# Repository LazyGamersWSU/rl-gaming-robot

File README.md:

# RL Gaming Robot

The RL Gaming Robot is a senior design project focused on developing a Reinforcement Learning system that learns to play games through repeated attempts and applies its learned behavior to a game to ultimately improve its score.

The current target game is Tetris. The long-term goal is for the RL agent to make gameplay decisions and output controller commands that are translated into physical actions pressed on a controller by a robotic system.

This repository contains the software and hardware elements used to create the project.

## Repository Structure

```text
RL-Gaming-Robot/

├── hardware/
│   ├── electronics/
│   ├── experiments/
│   ├── firmware/
│   ├── mechanical/
│   └── photos/
│ 
├── software/
│   ├── requirements/
│   ├── environment/
│   ├── agent/
│   └── test_cases/
│
└── README.md
```

## Hardware

The `hardware` directory contains the mechanical and electronic development files for the RL Gaming Robot.

This includes:

* Actuator experiments and testing
* CAD models and mechanical designs
* Controller mounting and interaction components
* Production hardware designs
* Hardware documentation and validation

See the [hardware README](hardware/README.md) for additional information.

## Software

The `software` directory contains the software required to develop and operate the RL system.

This includes:

* Python environment and dependency requirements
* Game environment code
* Reinforcement Learning agent code
* Software test cases

The software is responsible for interacting with the game environment, training and executing the RL agent, and producing controller actions for the hardware system.

See the [software README](software/README.md) for additional information.

## System Overview

The intended system operates as a feedback loop:

```text
┌─────────────────┐
│ Game Environment│
└────────┬────────┘
         │
         │ Game State
         ▼
┌─────────────────┐
│    RL Agent     │
└────────┬────────┘
         │
         │ Controller Action
         ▼
┌─────────────────┐
│ Robot Controller│
└────────┬────────┘
         │
         │ Physical Command
         ▼
┌─────────────────┐
│  Robotic System  │
└────────┬────────┘
         │
         │ Button Press
         ▼
┌─────────────────┐
│  NES Controller │
└────────┬────────┘
         │
         └──────────────► Game
```

The game produces a new state after each action, allowing the RL agent to continually evaluate the game and select its next action.

## Testing

Testing is an integral part of the project and is performed throughout both software and hardware development.

Software testing focuses on:

* Game-state processing
* RL agent behavior
* Action generation
* Software component integration
* Model performance and repeatability

Hardware testing focuses on:

* Actuator performance
* Button press accuracy
* Timing and reliability
* Mechanical positioning
* Hardware/software integration

Test cases are maintained within the appropriate software and hardware directories.

## Development Philosophy

The project is organized around **experimentation, validation, and integration**.

Development follows these general principles:

1. **Experiment** — Develop and test individual concepts and components.
2. **Validate** — Verify that components meet their intended requirements.
3. **Integrate** — Combine validated software and hardware components.
4. **Test** — Evaluate the complete system and identify integration issues.
5. **Iterate** — Use test results to improve the system.

Experimental implementations should be validated before being incorporated into the production system.

## Project Goals

The primary goals of the RL Gaming Robot project are to:

* Develop an RL agent capable of improving its gameplay through repeated attempts.
* Create a software environment for training and evaluating the agent.
* Develop a robotic system capable of physically interacting with a gaming controller.
* Establish reliable communication between the software and hardware systems.
* Test the performance and reliability of the complete system.
* Demonstrate the transfer of learned behavior from the software environment to physical gameplay.

## Current Development Status

The project is being developed incrementally, beginning with the software RL environment and agent before progressing toward full hardware integration.

Major development stages include:

1. Software environment development
2. RL agent development and training
3. Software testing and performance evaluation
4. Hardware development and validation
5. Software/hardware integration
6. Full-system testing
7. Final NES Tetris demonstration

## Team Roles

### Trystan Donmoyer - Software Development Lead
- Leads development of the reinforcement learning software and agent
- Develops training, inference, and game interaction systems
- Maintains the software architecture and coordinates software-side implementation

### Sam Culp - Hardware Development
- Leads hardware design and implementation of the physical gaming robot
- Designs and assembles the PCB, power distribution, actuator system, and mechanical components
- Develops and integrates Arduino firmware for hardware control and communication with the software system

### Matthew Dynes-Winberry - Integration & Testing
- Integrates the software and hardware systems into a complete working platform
- Develops and manages system-level testing and validation
- Troubleshoots issues across hardware/software interfaces and verifies system reliability

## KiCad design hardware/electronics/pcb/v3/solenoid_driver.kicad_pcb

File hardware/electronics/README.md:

# Electronics

The electronics system controls and powers the solenoid actuators used to physically operate the game controller.

## Subsystems

- [PCB](pcb/) — Solenoid driver PCB design and fabrication files with revision history
- [Power](power/power_budget.md) — Battery and system power requirements
- [Wiring](wiring/) — Electrical wiring and connections (visual)

## Signal Path

Arduino → MOSFET driver → Solenoids

## Power Path

Battery → BMS → Power switch → Fuse  → Solenoid driver PCB → Solenoids

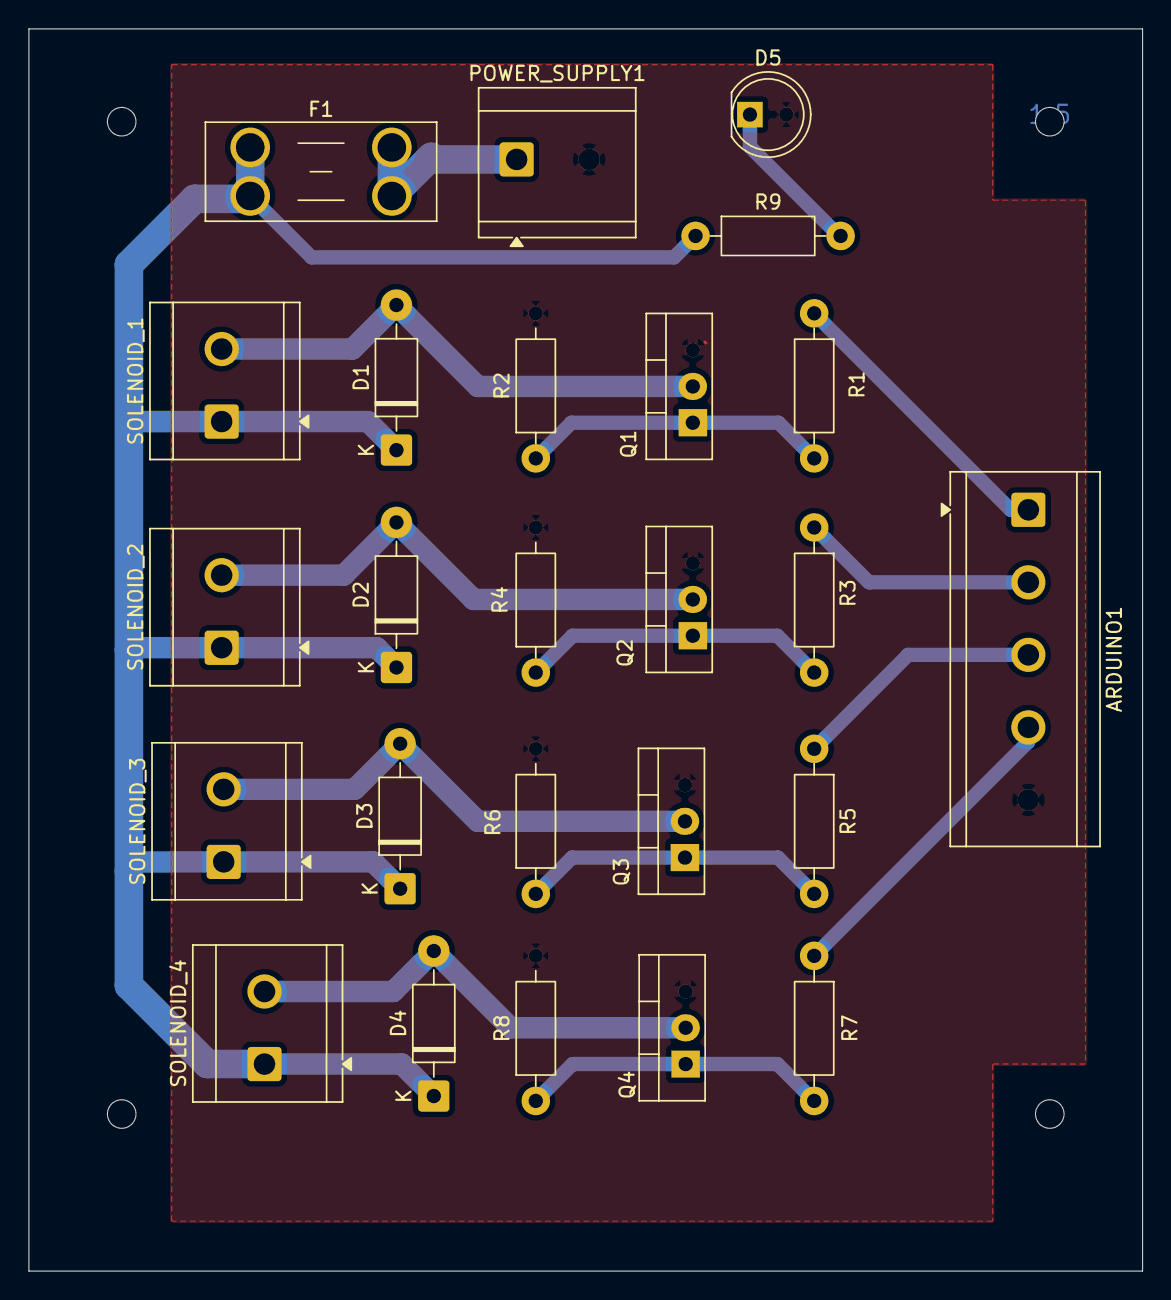
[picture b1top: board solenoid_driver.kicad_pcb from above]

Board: 2 copper layers, 78.0 x 87.0 mm, 25 parts (0 on the bottom side), 16 nets.

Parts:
ARDUINO1: Conn_01x05; TerminalBlock_CUI_TB007-508-05_1x05_P5.08mm_Horizontal
D1, D2, D3, D4: 1N4004; D_DO-41_SOD81_P10.16mm_Horizontal
D5: Green; LED_D5.0mm
F1: 7.5A; Fuseholder_Blade_Mini_Keystone_3568
POWER_SUPPLY1: Conn_01x02; TerminalBlock_CUI_TB007-508-02_1x02_P5.08mm_Horizontal
Q1, Q2, Q3, Q4: IRLZ44N; TO-220-3_Vertical
R1, R3, R5, R7: 220R; R_Axial_DIN0207_L6.3mm_D2.5mm_P10.16mm_Horizontal
R2, R4, R6, R8: 10k; R_Axial_DIN0207_L6.3mm_D2.5mm_P10.16mm_Horizontal
R9: 1k; R_Axial_DIN0207_L6.3mm_D2.5mm_P10.16mm_Horizontal
SOLENOID_1, SOLENOID_2, SOLENOID_3, SOLENOID_4: Conn_01x02; TerminalBlock_CUI_TB007-508-02_1x02_P5.08mm_Horizontal

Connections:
+12V: D1.1 (K), D2.1 (K), D3.1 (K), D4.1 (K), F1.1, R9.1, SOLENOID_1.1, SOLENOID_2.1, SOLENOID_3.1, SOLENOID_4.1
/SOL1: ARDUINO1.1, R1.1
/SOL2: ARDUINO1.2, R3.1
/SOL3: ARDUINO1.3, R5.1
/SOL4: ARDUINO1.4, R7.1
GND: ARDUINO1.5, D5.2 (A), POWER_SUPPLY1.2, Q1.3 (S), Q2.3 (S), Q3.3 (S), Q4.3 (S), R2.2, R4.2, R6.2, R8.1
unnamed: D1.2 (A), Q1.2 (D), SOLENOID_1.2
unnamed: D2.2 (A), Q2.2 (D), SOLENOID_2.2
unnamed: D3.2 (A), Q3.2 (D), SOLENOID_3.2
unnamed: D4.2 (A), Q4.2 (D), SOLENOID_4.2
unnamed: D5.1 (K), R9.2
unnamed: F1.2, POWER_SUPPLY1.1
unnamed: Q1.1 (G), R1.2, R2.1
unnamed: Q2.1 (G), R3.2, R4.1
unnamed: Q3.1 (G), R5.2, R6.1
unnamed: Q4.1 (G), R7.2, R8.1
